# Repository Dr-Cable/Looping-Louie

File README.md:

# Looping-Louie
modified Looping Louie with 8 player, random speed + turbo buttons for each player and light effects

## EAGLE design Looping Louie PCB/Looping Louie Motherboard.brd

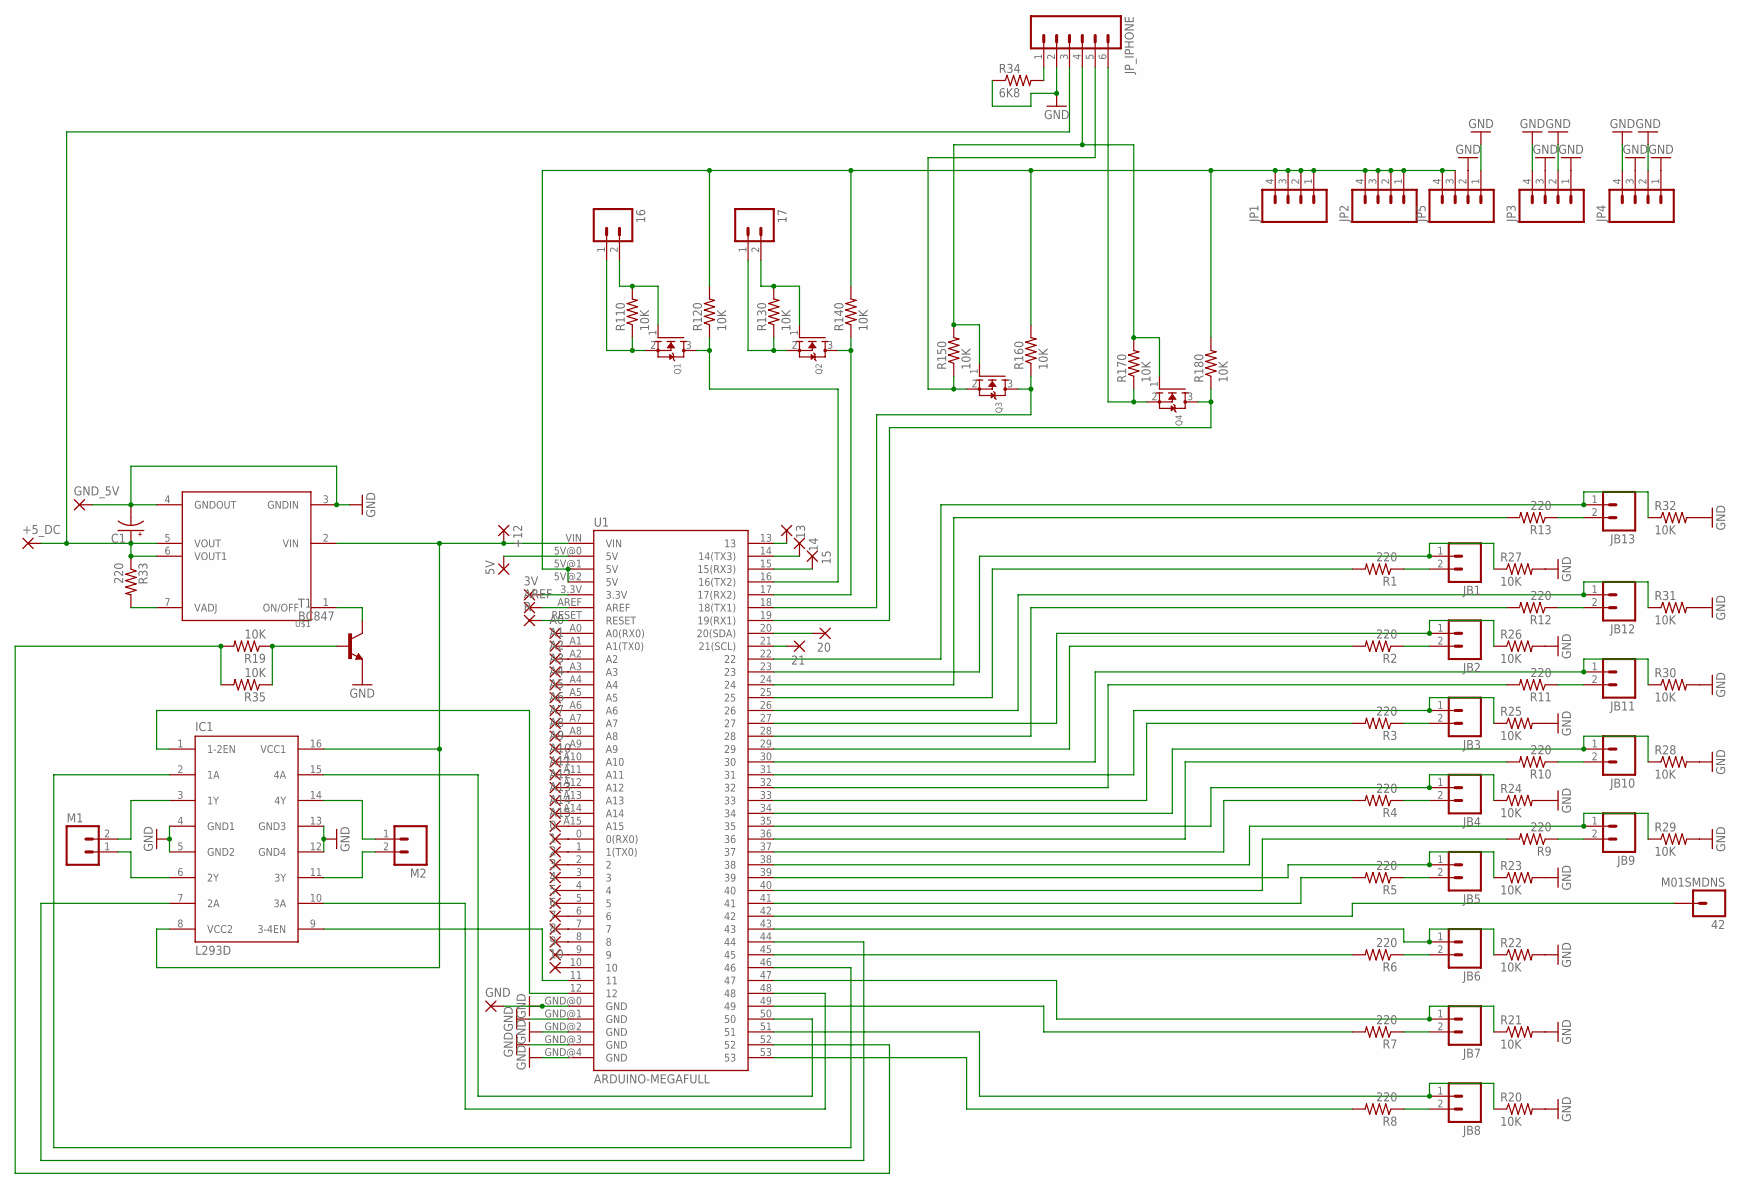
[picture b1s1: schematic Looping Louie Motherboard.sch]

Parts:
0, 1, 2, 3, 3V, 4, 5, 5V, 6, 7, 8, 9, 10, 13, 14, 15, 20, 21: 1,6/0,8
16, 17: M021X02_NO_SILK; 1X02_NO_SILK
42: M01SMDNS; 1X01NS
+5_DC, +12: 3,81/1,4
A0, A1, A2, A3, A4, A5, A6, A7, A8, A9, A10, A11, A12, A13, A14, A15: 1,6/0,8
AREF: 1,6/0,8
C1: CAP_POLG; PANASONIC_G
GND: 3,81/1,4
GND_5V: 3,81/1,4
IC1: L293D; DIL16
JB1, JB2, JB3, JB4, JB5, JB6, JB7, JB8, JB9, JB10, JB11, JB12, JB13: M021X02_NO_SILK; 1X02_NO_SILK
JP1, JP2, JP3, JP4, JP5: M041X04_NO_SILK; 1X04_NO_SILK
JP_IPHONE: M06LONGPADS; 1X06_LONGPADS
M1, M2: M02PTH3; 1X02_LONGPADS
Q1, Q2, Q3, Q4: MOSFET-NWAVE; SOT23-W
R: 1,6/0,8
R1, R2, R3, R4, R5, R6, R7, R8, R9, R10, R11, R12, R13, R33: 220; 0603-RES
R19, R20, R21, R22, R23, R24, R25, R26, R27, R28, R29, R30, R31, R32, R35, R110, R120, R130, R140, R150, R160, R170, R180: 10K; 0603-RES
R34: 6K8; 0603-RES
T1: BC847; SOT23
U1: ARDUINO-MEGAFULL; ARDUINO_MEGA_MIRROR
U$1: KIS-3R33S

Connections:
3V3_IPHONE: JP_IPHONE.4, Q3.1 (G), Q4.1 (G), R150.2, R170.2
5V: JP1.1, JP1.2, JP1.3, JP1.4, JP2.1, JP2.2, JP2.3, JP2.4, JP5.3, JP5.4, R120.2, R140.2, R160.2, R180.2, U1.5V@1 (5V), U1.5V@2 (5V)
12V: +12.1, IC1.8 (VCC2), IC1.16 (VCC1), U1.VIN, U$1.2 (VIN)
+5V_DC: +5_DC.1, C1.+, JP_IPHONE.3, R33.1, U$1.5 (VOUT), U$1.6 (VOUT1)
GND: C1.-, GND.1, GND_5V.1, IC1.4 (GND1), IC1.5 (GND2), IC1.12 (GND4), IC1.13 (GND3), JP3.1, JP3.2, JP3.3, JP3.4, JP4.1, JP4.2, JP4.3, JP4.4, JP5.1, JP5.2, JP_IPHONE.2, R20.2, R21.2, R22.2, R23.2, R24.2, R25.2, R26.2, R27.2, R28.2, R29.2, R30.2, R31.2, R32.2, R34.1, T1.2 (E), U1.GND@0 (GND), U1.GND@1 (GND), U1.GND@2 (GND), U1.GND@3 (GND), U1.GND@4 (GND), U$1.3 (GNDIN), U$1.4 (GNDOUT)
unnamed: JB1.1, R27.1, U1.23
unnamed: R1.2, U1.25
unnamed: JB2.1, R26.1, U1.27
unnamed: R2.2, U1.29
unnamed: JB3.1, R25.1, U1.31
unnamed: R3.2, U1.33
unnamed: JB1.2, R1.1
unnamed: JB2.2, R2.1
unnamed: JB3.2, R3.1
unnamed: R5.2, U1.41
unnamed: JB4.1, R24.1, U1.35
unnamed: JB5.1, R23.1, U1.39
unnamed: JB4.2, R4.1
unnamed: JB5.2, R5.1
unnamed: JB6.2, R6.1
unnamed: JB7.2, R7.1
unnamed: JB8.2, R8.1
unnamed: JB9.2, R9.1
unnamed: JB10.2, R10.1
unnamed: R8.2, U1.53
unnamed: IC1.10 (3A), U1.48
unnamed: R6.2, U1.45
unnamed: IC1.7 (2A), U1.44
unnamed: IC1.15 (4A), U1.50
unnamed: R7.2, U1.49
unnamed: JB7.1, R21.1, U1.47
unnamed: R4.2, U1.37
unnamed: JB8.1, R20.1, U1.51
unnamed: IC1.2 (1A), U1.46
unnamed: IC1.1 (1-2EN), U1.12
unnamed: Q4.3 (D), R180.1, U1.19 (19(RX1))
unnamed: IC1.9 (3-4EN), U1.11
unnamed: JP_IPHONE.1, R34.2
unnamed: 17.1, Q2.2 (S), R130.1
unnamed: Q2.3 (D), R140.1, U1.17 (17(RX2))
unnamed: 17.2, Q2.1 (G), R130.2
unnamed: Q1.3 (D), R120.1, U1.16 (16(TX2))
unnamed: 16.2, Q1.1 (G), R110.2
unnamed: R19.2, R35.2, U1.52
unnamed: JB10.1, R28.1, U1.34
unnamed: R11.2, U1.32
unnamed: JB11.1, R30.1, U1.30
unnamed: R12.2, U1.28
unnamed: JB12.1, R31.1, U1.26
unnamed: R13.2, U1.24
unnamed: JB13.1, R32.1, U1.22
unnamed: R19.1, R35.1, T1.1 (B)
unnamed: 16.1, Q1.2 (S), R110.1
unnamed: JB6.1, R22.1, U1.43
unnamed: 5V.1, U1.5V@0 (5V)
unnamed: IC1.14 (4Y), M2.1
unnamed: IC1.11 (3Y), M2.2
unnamed: IC1.6 (2Y), M1.1
unnamed: IC1.3 (1Y), M1.2
unnamed: T1.3 (C), U$1.1 (ON/OFF)
unnamed: R33.2, U$1.7 (VADJ)
unnamed: 0.1, U1.0 (0(RX0))
unnamed: 1.1, U1.1 (1(TX0))
unnamed: 2.1, U1.2
unnamed: 3.1, U1.3
unnamed: 4.1, U1.4
unnamed: 5.1, U1.5
unnamed: 6.1, U1.6
unnamed: 7.1, U1.7
unnamed: 8.1, U1.8
unnamed: 9.1, U1.9
unnamed: 10.1, U1.10
unnamed: 3V.1, U1.3.3V
unnamed: AREF.1, U1.AREF
unnamed: R.1, U1.RESET
unnamed: A0.1, U1.A0 (A0(RX0))
unnamed: A1.1, U1.A1 (A1(TX0))
unnamed: A2.1, U1.A2
unnamed: A3.1, U1.A3
unnamed: A4.1, U1.A4
unnamed: A5.1, U1.A5
unnamed: A6.1, U1.A6
unnamed: A7.1, U1.A7
unnamed: A8.1, U1.A8
unnamed: A9.1, U1.A9
unnamed: A10.1, U1.A10
unnamed: A11.1, U1.A11
unnamed: A12.1, U1.A12
unnamed: A13.1, U1.A13
unnamed: A14.1, U1.A14
unnamed: A15.1, U1.A15
unnamed: 13.1, U1.13
unnamed: 14.1, U1.14 (14(TX3))
unnamed: 15.1, U1.15 (15(RX3))
unnamed: 20.1, U1.20 (20(SDA))
unnamed: 21.1, U1.21 (21(SCL))
unnamed: Q3.3 (D), R160.1, U1.18 (18(TX1))
unnamed: R10.2, U1.36
unnamed: JB9.1, R29.1, U1.38
unnamed: R9.2, U1.40
unnamed: 42.1, U1.42
unnamed: JB13.2, R13.1
unnamed: JB12.2, R12.1
unnamed: JB11.2, R11.1
RX_IPHONE: JP_IPHONE.6, Q4.2 (S), R170.1
TX_IPHONE: JP_IPHONE.5, Q3.2 (S), R150.1

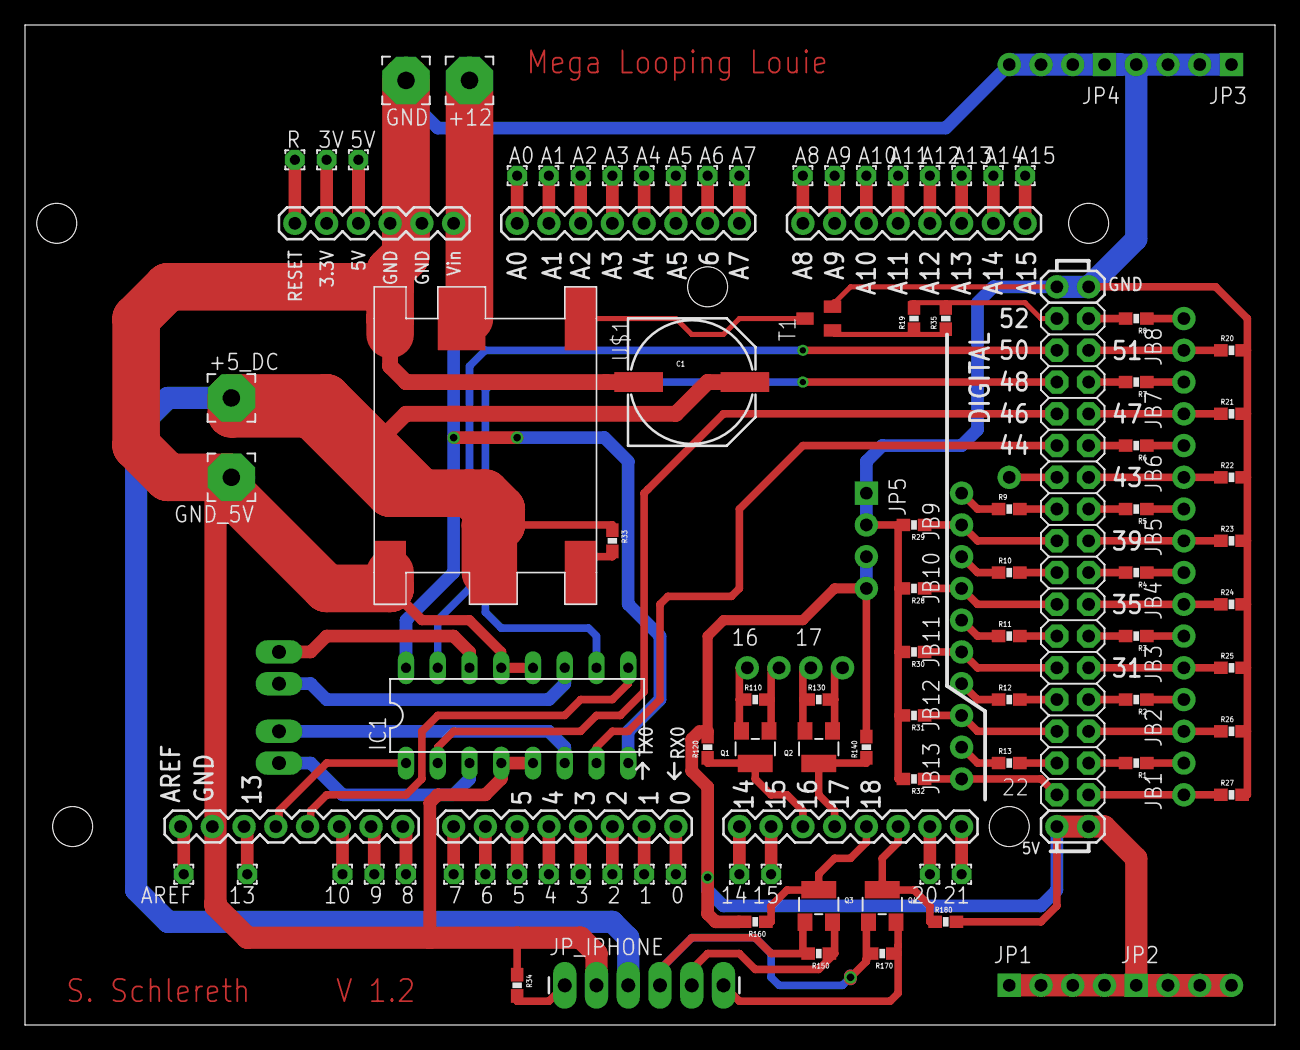
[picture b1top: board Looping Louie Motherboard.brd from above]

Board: 2 copper layers, 100.0 x 80.0 mm, 111 parts (0 on the bottom side), 106 nets.

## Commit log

2015-03-04 first working commithopefully
2015-03-04 second commit with all files
2015-03-04 try to push whole folder
2015-03-04 Added PCB files
2015-03-04 remove folder
2015-03-05 Video upload
2015-03-05 Add picture
2016-01-08 Changes before Ski vacation
2021-01-27 Add PDF of Schematics with all parts

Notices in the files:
parts and their libraries:
SparkFun: Licensing: CC v3.0 Share-Alike You are welcome to use this library for commercial purposes.
